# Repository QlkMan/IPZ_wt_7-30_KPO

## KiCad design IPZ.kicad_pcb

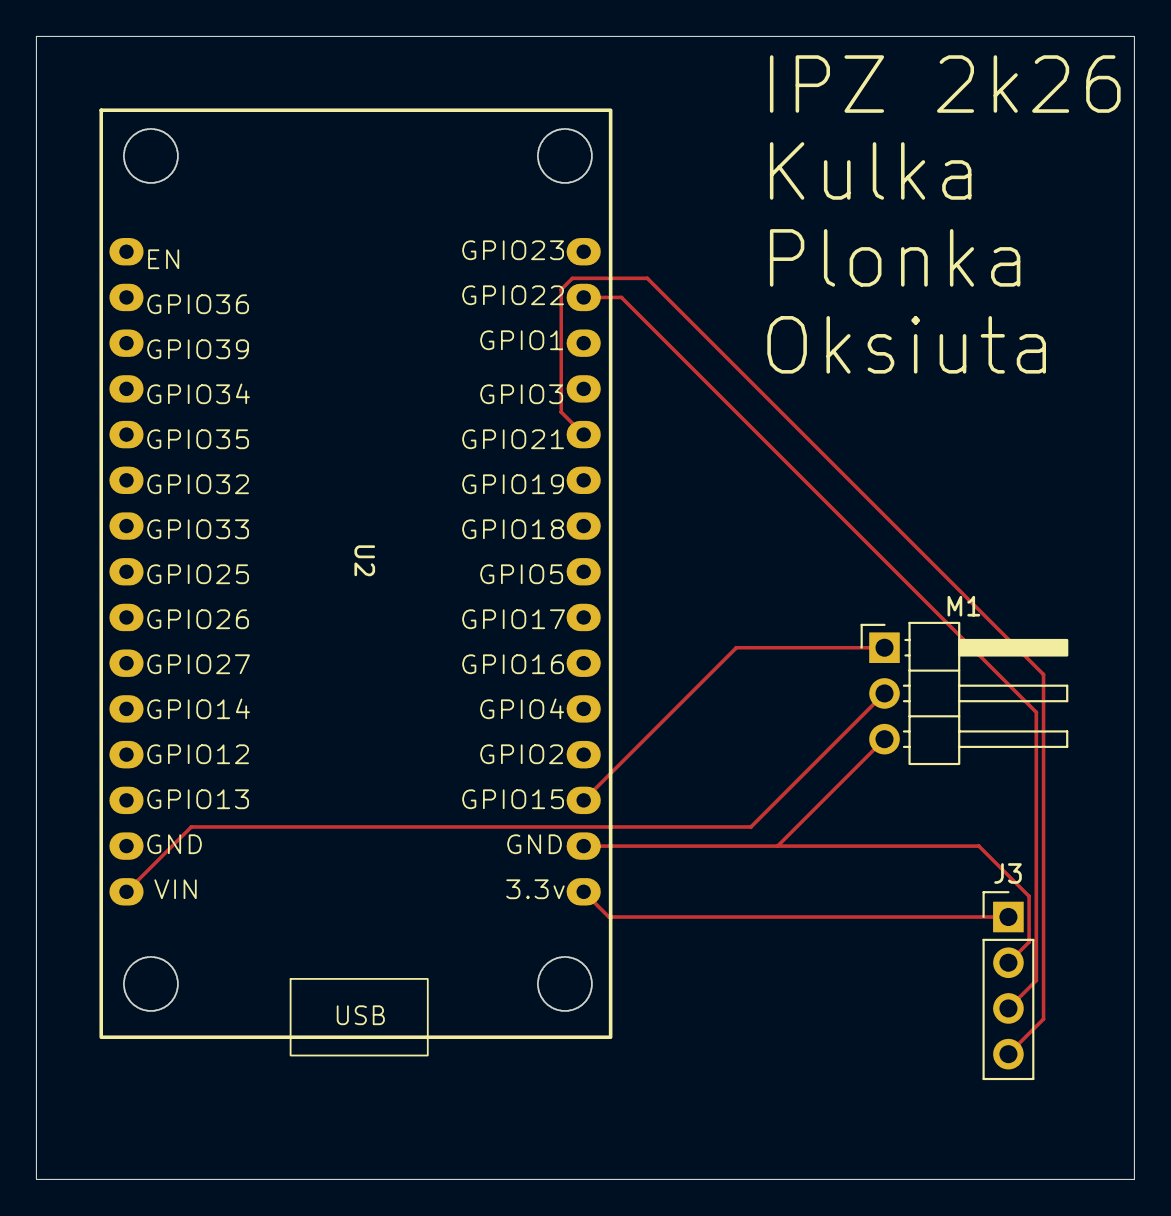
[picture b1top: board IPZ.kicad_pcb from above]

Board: 2 copper layers, 60.9 x 63.5 mm, 3 parts (0 on the bottom side), 6 nets.

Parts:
J3: Conn_01x04_Pin; PinHeader_1x04_P2.54mm_Vertical
M1: Motor_Servo; PinHeader_1x03_P2.54mm_Horizontal
U2: ESP32_30pin

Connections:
unnamed: J3.1, U2.16 (3.3v)
unnamed: J3.2, M1.3 (-), U2.17 (GND)
unnamed: J3.3, U2.29 (GPIO22)
unnamed: J3.4, U2.26 (GPIO21)
unnamed: M1.2 (+), U2.1 (VIN)
unnamed: M1.1 (PWM), U2.18 (GPIO15)

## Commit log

2026-06-23 Add files via upload
    PCB schemat
2026-06-23 Schemat PCB
2026-06-23 Płytka PCB
2026-06-24 Model 3D obudowy
2026-06-24 Dokumentacja projektu
